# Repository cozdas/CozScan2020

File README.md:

# CozScan2020

This is a do-it-yourself 20-channel solid-state scanner card compatible with Keithley 2000-SCAN-20 and thus should work with Keithley 2000, 2001, 2002, 2010 and DMM6500 bench multimeters. **Currently this design is tested only on DMM6500.**

|**== Warning ==**|
|-|
| **If you decide to build and/or use this card do it at your own risk. I do not guarantee that this design works properly and I can't guarantee that using this won't result any damages to the equipment or won't cause injury. Electrical or thermal limits of this design are unknown/unspecified. So please make sure that you understand the design before attempting to build and/or use it.**|

## History behind the project
I've always had a multimeter since highschool, where I studied electronics. But all of them were handheld devices. So recently I decided to get a bench multimeter and Keithley DMM6500 seemed like a perfect choice for my needs. I liked the scanner card support which makes the unit work as a small data acqusition system. I bought a used 2000-SCAN card from eBay and it worked perfectly, I was able to record multiple quantities over long time spans and analyse their dependencies (such as tempco measurement ). But there was one problem: the original SCAN-2000 card has mechanical relays and they are loud therefore logging multiple channels overnight in my office, which is near our bedroom, was an annoying dripping-tap simulator. So I decided to build myself a silent solid-state version.

The original Keithley SCAN-2000 card has a very basic design: few serial-to-parallel shift registers and bunch of bi-stable (latching) mechanical relays. The control signal from the DMM has 3 lines: clock, data and strobe. The card's manual has the full schematic; by looking at the schematic you can determine which bit does what. After realizing that the 20-channel scan-2020 card uses the same interface and the same basic circuit design, I decided to implement a 20 channel card, the more the merrier. The DMM determines the installed card type using the ID pins (13 and 29) on the connector. 

## Reverse Engineering the Communication

The schematic shows all the connections and logic but doesn't tell much about the timings and how the DMM drives the relays. For that reason I just sniffed the clock, data and strobe lines both in scan-2000 and scan-2020 mode using both my oscillascope and a cheap logic analyser. You can find the [logic analyser logs](Documents/LogicAnalyserLogs/) in the Documents folder. You can open the files with [Saleae Logic software](https://www.saleae.com/downloads/)

Here are the key timing figures:

* Clock: 100kHz, %33 duty
* Data: 10us, centered around clock pulse
* Relay coil current duration: 4ms
* Strobe Pulse: 3.333ms
* Channel off to channel on: ~1.7ms

## Circuit Design

Initially I was planning to replicate the same circuit, using the same or similar components. One problem with that approach was that unlike the mechanical latching relays, the solid state relays are not latching thus I had add latches to the circuit so that the turned on relay stays on even after the DMM sets the coil off. This quickly increased the number of compoments required for the board. 

So instead of following the same design with primitive logic elements, I decided to switch to a microcontroller + software solution. I needed a cheap microcontroller with at least 25 IO pins (20 outputs for the channels, 2 outputs for directing the upper channels either to input or to sense and 3 input pins for DMM communication). The most convenient solution turned out to be using a cheap arduino micro compatible board with ATmega32U4 MCU. One minor problem with that board was that only 24 of the 26 IO pins of the ATmega32U4 were exposed on the board pinout and that was unfortunately 1 short of what I needed. But after checking the Arduino Micro schematic I saw that it's easy to pull a wire from the TX led to one of the unused pins, exposing PD5 signal and thus increasing the IO pin count to needed 25.

One gothca you need to be careful while choosing a MCU board is that some boards with certain bootloader firmware (Such as Arduino Uno) will blink the LED while booting. Make sure that the board+firmware you have doesn't have this behavior.

As SSRs I picked Toshiba TLP3558A as it seemed to be at the sweet spot of on-resistance, price and leakage current. It might not be the best choice, feel free to modify that to your taste.

## PCB Design
This is a "Do-It-Yourself as much as you can" project, thus I wanted to make my own PCB. Since I can't do through-hole plating I designed the layout such that the pins of the components are used as the vias and for this reason I preferred through-hole components. A more tidy and even compact layout with SMD components should be possible if the PCB will be manufactured professionally. First I tried to use Eagle CAD, which I was already familiar with, but the free version is not supporting boards this big. Internets(tm) seems to agree on the KiCAD as one of the best options, thus I learned how to use KiCAD and used it for this project.

You can find the KiCAD project files in the [KiCAD folder](KiCad/). Since this is my very first KiCAD design, I'm sure that there are some mistakes/not-so-correct things I've done. Let me know if you spot any.

## Software

My first attemp was an interrupt-driven software but it was behaving erratically. After a short debugging session I found the source of the problem: the MCU was not fast enough and was missing the clocks. I tried to optimize the code as much as I can with some bit-magic etc but it was still missing the clocks. So I decided to switch to active polling mode and disable the inturrupts completely, making the system more suitable for a realtime application. Polling the clock edges in an active loop indeed worked properly and it was fast enough that I was able to squeeze in some sanity checking routine to the code; making sure that we collected correct number of bits before the strobe, only one channel is connected to the input or sense terminals etc.

The Arduino studio source is located in the [Arduino](Arduino/) folder.

## Bill of Materials
- DMM Connector: 1x [Molex 85050](https://www.digikey.com/product-detail/en/molex/0850500000/WM20488-ND/2790645)
- Solid State Relay: 24x [Toshiba TLP3558A](https://www.digikey.com/product-detail/en/toshiba-semiconductor-and-storage/TLP3558A-F/TLP3558A-F-ND/8539925)
- Cable Terminal Blocks: 
  - 12 Pos: 2x [Phoenix Contact 1869318](https://www.digikey.com/product-detail/en/phoenix-contact/1869318/277-6361-ND/349230)
  - 10 Pos: 2x [Phoenix Contact 1869295](https://www.digikey.com/product-detail/en/phoenix-contact/1869295/277-6063-ND/349229)
- Controller: 1x [Arduino Micro](https://store.arduino.cc/usa/arduino-micro) (or [a clone](https://www.amazon.com/dp/B00J1X5B7Y))
- Resistors
  - 22x 120 Ohm 1/4W
  - 3x 1 kOhm 1/4W
- Capacitor: 1uF 16V
- PCB: 205mm x 70mm x 1.5mm, dual-sided

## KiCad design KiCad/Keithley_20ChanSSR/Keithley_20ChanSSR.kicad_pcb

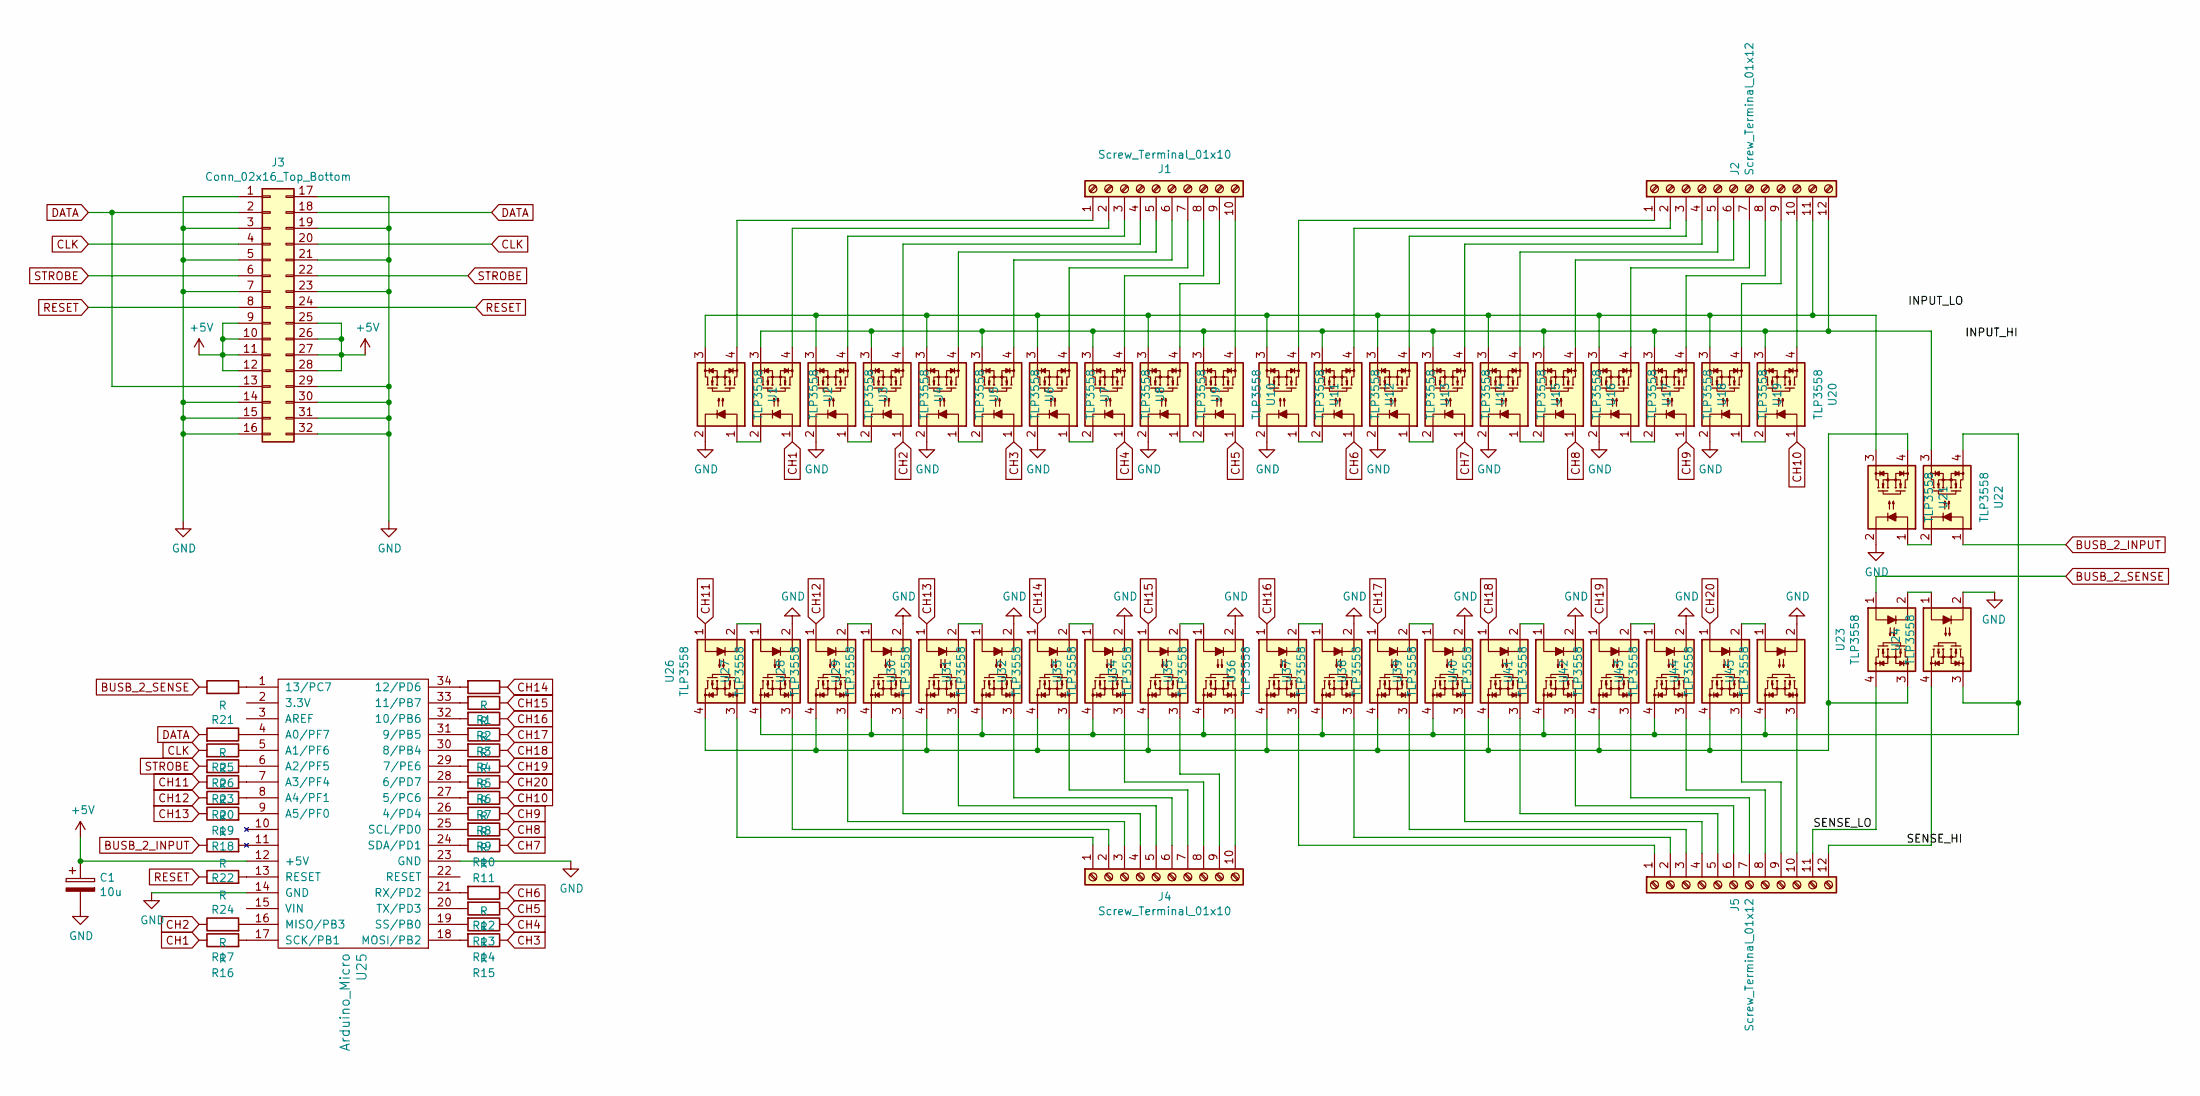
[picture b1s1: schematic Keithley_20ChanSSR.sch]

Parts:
C1: 10u; CP_EIA-6032-20_AVX-F
J1, J4: Screw_Terminal_01x10; TerminalBlock_Phoenix_MKDS-3-10-5.08_1x10_P5.08mm_Horizontal
J2, J5: Screw_Terminal_01x12; TerminalBlock_Phoenix_MKDS-1,5-12-5.08_1x12_P5.08mm_Horizon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
J3: Conn_02x16_Top_Bottom; DIN41612_B2_2x16_Horizontal
R1, R2, R3, R4, R5, R6, R7, R8, R9, R10, R11, R12, R13, R14, R15, R16, R17, R18, R19, R20, R21, R22, R23, R24, R25, R26: R; R_Axial_DIN0207_L6.3mm_D2.5mm_P10.16mm_Horizontal
U1, U2, U3, U4, U5, U6, U7, U8, U9, U10, U11, U12, U13, U14, U15, U16, U17, U18, U19, U20, U21, U22, U23, U24, U26, U27, U28, U29, U30, U31, U32, U33, U34, U35, U36, U37, U38, U39, U40, U41, U42, U43, U44, U45: TLP3558; DIP-4_W7.62mm_LongPads_coz
U25: Arduino_Micro; Arduino_Micro_Socket_coz

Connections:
+5V: C1.1, J3.9, J3.10, J3.11, J3.12, J3.25, J3.26, J3.27, J3.28, U25.12 (+5V)
/SENSE_LO: J5.11, U23.4
BUSB_2_INPUT: R22.1, U22.1
BUSB_2_SENSE: R21.1, U23.1
CH1: R16.1, U2.1
CH2: R17.1, U4.1
CH3: R15.1, U6.1
CH4: R14.1, U8.1
CH5: R13.1, U10.1
CH6: R12.1, U12.1
CH7: R11.1, U14.1
CH8: R10.1, U16.1
CH9: R9.1, U18.1
CH10: R8.1, U20.1
CH11: R20.1, U26.1
CH12: R19.1, U28.1
CH13: R18.1, U30.1
CH14: R1.1, U32.1
CH15: R2.1, U34.1
CH16: R3.1, U36.1
CH17: R4.1, U38.1
CH18: R5.1, U40.1
CH19: R6.1, U42.1
CH20: R7.1, U44.1
CLK: J3.4, J3.20, R26.2
DATA: J3.2, J3.13, J3.18, R25.2
GND: C1.2, J3.1, J3.3, J3.5, J3.7, J3.14, J3.15, J3.16, J3.17, J3.19, J3.21, J3.23, J3.29, J3.30, J3.31, J3.32, U1.2, U3.2, U5.2, U7.2, U9.2, U11.2, U13.2, U15.2, U17.2, U19.2, U21.2, U24.2, U25.14 (GND), U25.23 (GND), U27.2, U29.2, U31.2, U33.2, U35.2, U37.2, U39.2, U41.2, U43.2, U45.2
unnamed: J1.1, U1.4
unnamed: J1.2, U2.4
unnamed: J1.3, U3.4
unnamed: J1.4, U4.4
unnamed: J1.5, U5.4
unnamed: J1.6, U6.4
unnamed: J1.7, U7.4
unnamed: J1.8, U8.4
unnamed: J1.9, U9.4
unnamed: J1.10, U10.4
unnamed: J2.1, U11.4
unnamed: J2.2, U12.4
unnamed: J2.3, U13.4
unnamed: J2.4, U14.4
unnamed: J2.5, U15.4
unnamed: J2.6, U16.4
unnamed: J2.7, U17.4
unnamed: J2.8, U18.4
unnamed: J2.9, U19.4
unnamed: J2.10, U20.4
unnamed: J2.11, U1.3, U3.3, U5.3, U7.3, U9.3, U11.3, U13.3, U15.3, U17.3, U19.3, U21.3
unnamed: J2.12, U2.3, U4.3, U6.3, U8.3, U10.3, U12.3, U14.3, U16.3, U18.3, U20.3, U22.3
unnamed: J4.1, U26.3
unnamed: J4.2, U27.3
unnamed: J4.3, U28.3
unnamed: J4.4, U29.3
unnamed: J4.5, U30.3
unnamed: J4.6, U31.3
unnamed: J4.7, U32.3
unnamed: J4.8, U33.3
unnamed: J4.9, U34.3
unnamed: J4.10, U35.3
unnamed: J5.1, U36.3
unnamed: J5.2, U37.3
unnamed: J5.3, U38.3
unnamed: J5.4, U39.3
unnamed: J5.5, U40.3
unnamed: J5.6, U41.3
unnamed: J5.7, U42.3
unnamed: J5.8, U43.3
unnamed: J5.9, U44.3
unnamed: J5.10, U45.3
unnamed: J5.12, U24.4
unnamed: R1.2, U25.34 (12/PD6)
unnamed: R2.2, U25.33 (11/PB7)
unnamed: R3.2, U25.32 (10/PB6)
unnamed: R4.2, U25.31 (9/PB5)
unnamed: R5.2, U25.30 (8/PB4)
unnamed: R6.2, U25.29 (7/PE6)
unnamed: R7.2, U25.28 (6/PD7)
unnamed: R8.2, U25.27 (5/PC6)
unnamed: R9.2, U25.26 (4/PD4)
unnamed: R10.2, U25.25 (SCL/PD0)
unnamed: R11.2, U25.24 (SDA/PD1)
unnamed: R12.2, U25.21 (RX/PD2)
unnamed: R13.2, U25.20 (TX/PD3)
unnamed: R14.2, U25.19 (SS/PB0)
unnamed: R15.2, U25.18 (MOSI/PB2)
unnamed: R16.2, U25.17 (SCK/PB1)
unnamed: R17.2, U25.16 (MISO/PB3)
unnamed: R18.2, U25.9 (A5/PF0)
unnamed: R19.2, U25.8 (A4/PF1)
unnamed: R20.2, U25.7 (A3/PF4)
unnamed: R21.2, U25.1 (13/PC7)
unnamed: R22.2, U25.11
unnamed: R23.1, U25.6 (A2/PF5)
unnamed: R24.2, U25.13 (RESET)
unnamed: R25.1, U25.4 (A0/PF7)
unnamed: R26.1, U25.5 (A1/PF6)
unnamed: U1.1, U2.2
unnamed: U3.1, U4.2
unnamed: U5.1, U6.2
unnamed: U7.1, U8.2
unnamed: U9.1, U10.2
unnamed: U11.1, U12.2
unnamed: U13.1, U14.2
unnamed: U15.1, U16.2
unnamed: U17.1, U18.2
unnamed: U19.1, U20.2
unnamed: U21.1, U22.2
unnamed: U21.4, U23.3, U26.4, U28.4, U30.4, U32.4, U34.4, U36.4, U38.4, U40.4, U42.4, U44.4
unnamed: U22.4, U24.3, U27.4, U29.4, U31.4, U33.4, U35.4, U37.4, U39.4, U41.4, U43.4, U45.4
unnamed: U23.2, U24.1
unnamed: U26.2, U27.1
unnamed: U28.2, U29.1
unnamed: U30.2, U31.1
unnamed: U32.2, U33.1
unnamed: U34.2, U35.1
unnamed: U36.2, U37.1
unnamed: U38.2, U39.1
unnamed: U40.2, U41.1
unnamed: U42.2, U43.1
unnamed: U44.2, U45.1
RESET: J3.8, J3.24, R24.1
STROBE: J3.6, J3.22, R23.2

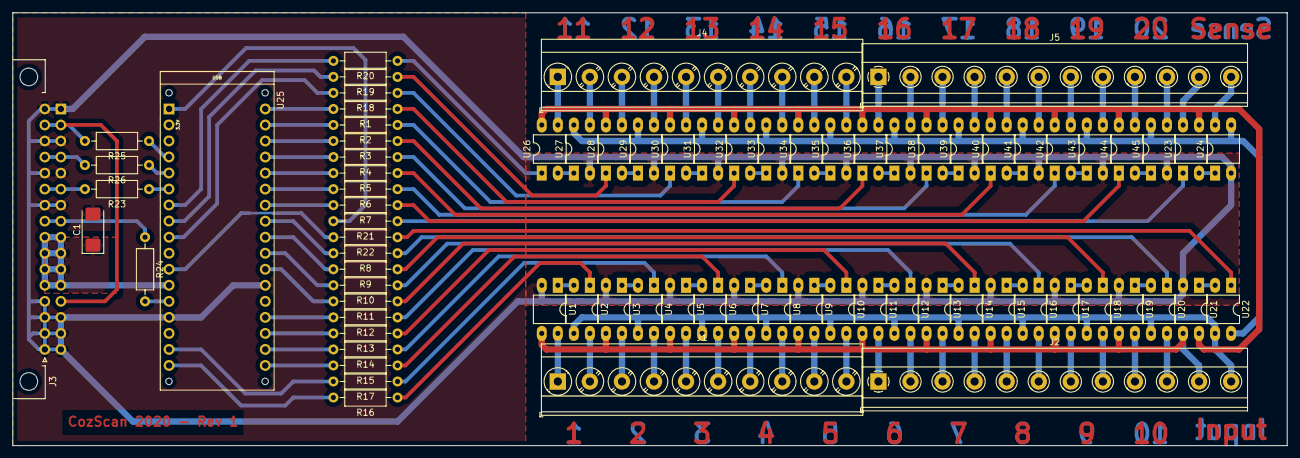
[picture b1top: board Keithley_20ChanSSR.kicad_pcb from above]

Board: 2 copper layers, 201.9 x 68.6 mm, 77 parts (0 on the bottom side), 122 nets.

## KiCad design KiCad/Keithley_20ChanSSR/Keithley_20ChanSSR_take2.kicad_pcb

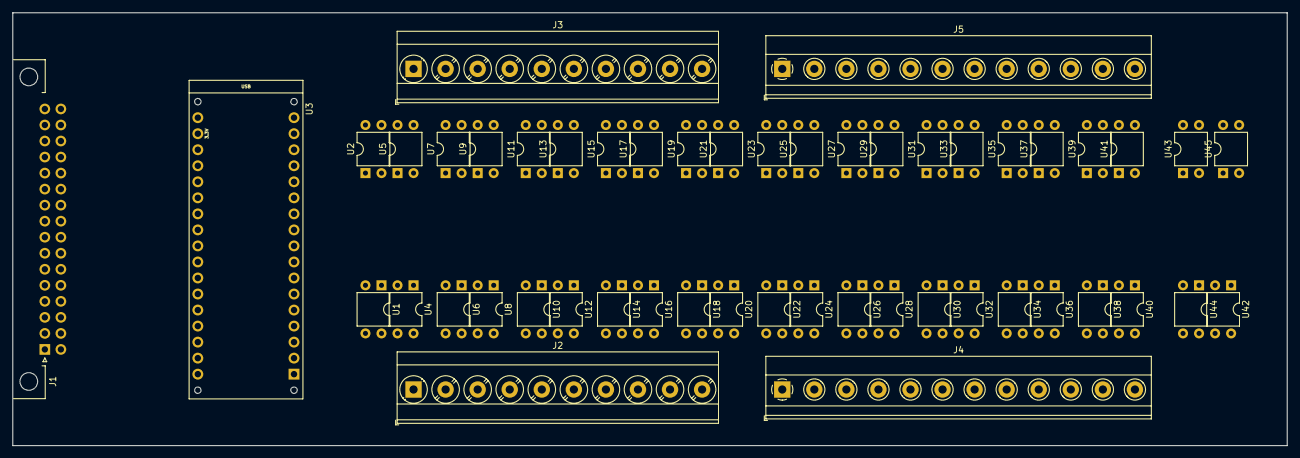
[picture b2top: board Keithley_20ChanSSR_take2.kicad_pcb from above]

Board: 2 copper layers, 201.9 x 68.6 mm, 50 parts (0 on the bottom side), 77 nets, no tracks yet.

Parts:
J1: Conn_02x16_Top_Bottom; DIN41612_B2_2x16_Horizontal
J2, J3: Screw_Terminal_01x10; TerminalBlock_Phoenix_MKDS-3-10-5.08_1x10_P5.08mm_Horizontal
J4, J5: Screw_Terminal_01x12; TerminalBlock_Phoenix_MKDS-1,5-12-5.08_1x12_P5.08mm_Horizon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
U1, U2, U4, U5, U6, U7, U8, U9, U10, U11, U12, U13, U14, U15, U16, U17, U18, U19, U20, U21, U22, U23, U24, U25, U26, U27, U28, U29, U30, U31, U32, U33, U34, U35, U36, U37, U38, U39, U40, U41, U42, U43, U44, U45: TLP3558; DIP-4_W7.62mm
U3: Arduino_Micro; Arduino_Micro_Socket

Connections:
+5V: J1.9, J1.10, J1.11, J1.12, J1.25, J1.26, J1.27, J1.28, U3.5V
/BUSB_HI: U5.3, U9.3, U13.3, U17.3, U21.3, U25.3, U29.3, U33.3, U37.3, U41.3, U44.4, U45.3
/BUSB_LO: U2.3, U7.3, U11.3, U15.3, U19.3, U23.3, U27.3, U31.3, U35.3, U39.3, U42.4, U43.4
/INPUT_HI: J4.11, J4.12, U1.4, U4.4, U6.3, U8.3, U10.3, U12.3, U14.3, U16.3, U18.3, U20.3, U22.3, U24.3, U26.3, U28.3, U30.3, U32.3, U34.3, U36.3, U38.3, U40.3, U42.3, U44.3
/SENSE_HI: J5.12, U45.4
/SENSE_LO: J5.11, U43.3
CLK: J1.4, J1.20, U3.A1
DATA: J1.2, J1.13, J1.18, U3.A0
GND: J1.1, J1.3, J1.5, J1.7, J1.14, J1.15, J1.16, J1.17, J1.19, J1.21, J1.23, J1.29, J1.30, J1.31, J1.32, U1.1, U5.2, U6.2, U9.2, U13.2, U14.2, U17.2, U18.2, U21.2, U24.2, U25.2, U28.2, U29.2, U32.2, U33.2, U36.2, U37.2, U40.2, U41.2, U44.2, U45.2
unnamed: J2.1, U1.3
unnamed: J2.2, U4.3
unnamed: J2.3, U6.4
unnamed: J2.4, U8.4
unnamed: J2.5, U10.4
unnamed: J2.6, U12.4
unnamed: J2.7, U14.4
unnamed: J2.8, U16.4
unnamed: J2.9, U18.4
unnamed: J2.10, U20.4
unnamed: J3.1, U2.4
unnamed: J3.2, U5.4
unnamed: J3.3, U7.4
unnamed: J3.4, U9.4
unnamed: J3.5, U11.4
unnamed: J3.6, U13.4
unnamed: J3.7, U15.4
unnamed: J3.8, U17.4
unnamed: J3.9, U19.4
unnamed: J3.10, U21.4
unnamed: J4.1, U22.4
unnamed: J4.2, U24.4
unnamed: J4.3, U26.4
unnamed: J4.4, U28.4
unnamed: J4.5, U30.4
unnamed: J4.6, U32.4
unnamed: J4.7, U34.4
unnamed: J4.8, U36.4
unnamed: J4.9, U38.4
unnamed: J4.10, U40.4
unnamed: J5.1, U23.4
unnamed: J5.2, U25.4
unnamed: J5.3, U27.4
unnamed: J5.4, U29.4
unnamed: J5.5, U31.4
unnamed: J5.6, U33.4
unnamed: J5.7, U35.4
unnamed: J5.8, U37.4
unnamed: J5.9, U39.4
unnamed: J5.10, U41.4
unnamed: U1.2, U4.1
unnamed: U2.1, U3.A3
unnamed: U2.2, U5.1
unnamed: U3.A4, U7.1
unnamed: U6.1, U8.2
unnamed: U7.2, U9.1
unnamed: U10.1, U12.2
unnamed: U3.A5, U11.1
unnamed: U11.2, U13.1
unnamed: U14.1, U16.2
unnamed: U15.2, U17.1
unnamed: U18.1, U20.2
unnamed: U3.SCK, U19.1
unnamed: U19.2, U21.1
unnamed: U22.2, U24.1
unnamed: U23.2, U25.1
unnamed: U26.2, U28.1
unnamed: U3.SS, U27.1
unnamed: U27.2, U29.1
unnamed: U30.2, U32.1
unnamed: U31.2, U33.1
unnamed: U34.2, U36.1
unnamed: U35.2, U37.1
unnamed: U38.2, U40.1
unnamed: U39.2, U41.1
unnamed: U43.2, U45.1
RESET: J1.8, J1.24
STROBE: J1.6, J1.22, U3.A2

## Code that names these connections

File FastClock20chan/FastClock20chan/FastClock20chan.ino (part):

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/* SCAN CHANNEL TO PIN MAPPING
chan DPin   NAME  PORT    BIT   MicroPin
0     --, 
1     15    PB1   PORTB   1     17  B:1320 D:32104 C:6 
2     14    PB3   PORTB   3     16
3     16    PB2   PORTB   2     18
4     17    PB0   PORTB   0     19
5     1     PD3   PORTD   3     21
6     0     PD2   PORTD   2     20
7     2     PD1   PORTD   1     24
8     3     PD0   PORTD   0     25
9     4     PD4   PORTD   4     26
10    5     PC6   PORTC   6     27

11    21    PF4   PORTF   4     7   B:7654 C: D:67 E:6 F:410 
12    22    PF1   PORTF   1     8
13    23    PF0   PORTF   0     9
14    12    PD6   PORTD   6     34
15    11    PB7   PORTB   7     33
16    10    PB6   PORTB   6     32
17    9     PB5   PORTB   5     31
18    8     PB4   PORTB   4     30
19    7     PE6   PORTE   6     29
20    6     PD7   PORTD   7     28

21    13    PC7   PORTC   7     1
22    30    PD5   PORTD   5     (11: wire from TX led)
*/

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//even bits: reset coil
//odd bits: set coil
//ctrl bit, chan, Dpin, PORTBIT,  PORT,   BIT
0           11    21    PF4       PORTF   4
2           12    22    PF1       PORTF   1
4           13    23    PF0       PORTF   0
6           14    12    PD6       PORTD   6
8           15    11    PB7       PORTB   7
10          16    10    PB6       PORTB   6
12          17    9     PB5       PORTB   5
14          18    8     PB4       PORTB   4
16          19    7     PE6       PORTE   6
18          20    6     PD7       PORTD   7
20          1     15    PB1       PORTB   1
22          2     14    PB3       PORTB   3 
24          3     16    PB2       PORTB   2
26          4     17    PB0       PORTB   0
28          5     1     PD3       PORTD   3
30          6     0     PD2       PORTD   2
32          7     2     PD1       PORTD   1
34          8     3     PD0       PORTD   0
36          9     4     PD4       PORTD   4
38          10    5     PC6       PORTC   6
40          21    13    PC7       PORTC   7 //4WIRE
*/

//temp variables to hold register set/clear bits
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      (*controlbit2port[i]) |= (st&1)<<(controlbit2portbit[i]);
    }

    //BusB2In = !BusB2Sense (PD5 = !PC7)
    //_PD = (PD&~(1<<5)) | (((~_PC)&(1<<7))>>2);
    if(_PC&(1<<7))
      _PD &= ~(1<<5);
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  }

  //set the input pins
  pinMode(18, INPUT); //A0: PF7: DATA
  pinMode(19, INPUT); //A1: PF6: CLOCK
  pinMode(20, INPUT); //A2: PF5: STROBE

  //port states
  _PB = _PC = _PD = _PE = _PF = 0;
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
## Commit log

2019-05-15 - First version of CozScan2020 card and the arduino Micro code to drive the relays. Seems working fine
2019-08-26 - reworked the logic in the strobe call to have the system more robust. - Added sanity checks to strobe making sure that not two channels are connected to a single bus - if no channels on Bus B are t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
2019-08-26 - added bunch of photos and videos during making of the card
2019-08-28 shuffled files around for cleaner organization
2019-10-24 Update README.md
    Improved the readme file. Still heavily work in progress
2019-12-24 Minor improvements to readme
2019-12-24 Added some more photos
2019-12-24 more tweaks
2019-12-26 Deleted some unused files, added the required library.
2019-12-26 Added the License
2019-12-26 more work on readme, moved doc files around
2019-12-26 updated readme, added schematics, removed eagle files
2019-12-26 more tweaks to readme
2019-12-27 Cleaned up the schematic for better readibility
2019-12-27 updated the BOM
